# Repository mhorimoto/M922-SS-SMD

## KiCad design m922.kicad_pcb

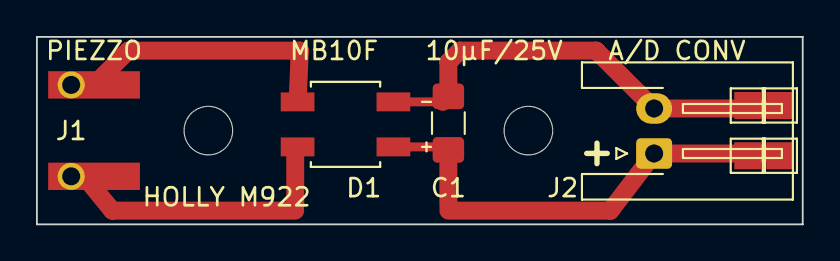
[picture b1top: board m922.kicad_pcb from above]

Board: 2 copper layers, 42.5 x 10.4 mm, 5 parts (0 on the bottom side), 4 nets.

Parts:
C1: 10μF/25V; C_1206_3216Metric_Pad1.42x1.75mm_HandSolder
D1: MB10F; DIOB_MB10F-13
J1: PIEZZO; LDT0-028K_MID
J2: A/D CONV; JST_XH_S2B-XH-A-1_1x02_P2.50mm_Horizontal
TP1: TestPoint_Pad_1.5x1.5mm

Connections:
unnamed: C1.1, D1.1, J2.1, TP1.1
unnamed: C1.2, D1.3, J2.2
unnamed: D1.2, J1.2
unnamed: D1.4, J1.1

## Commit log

2021-09-16 試作第一案
2021-09-19 Rev.1 PCBGOGO ordering data
2023-02-13 sche: KiCAD new version
2024-06-21 KiCAD v8
